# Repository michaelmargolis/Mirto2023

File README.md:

# Mirto2023
This repository contains software and CAD files for the 2023 version of
the Middlesex University robot platform used for CS and outreach.

This version supports the following variants:
* CS Mirto using Teensy 3.2 board and Raspberry Pi 
  * Teensy drives robot hardware
  * Pi supports robot logic in high level language (python, racket etc)
  * Communication between teensy and Pi using ASIP protocol (see ASIP 1.2 repo)
  * two legacy PCBs are supported:
    * Mirto2016 board that uses Toshiba TB6612FNG H-Bridge
    * Mirto2018 board using TI DRV8833 H-Bridge
  
* CS Mirto using Pico 2040 and Raspbery Pi
  * similar to above but using Pico instead of Teensy
  
* Outreach Mirto using Pico WiFI
  * Uses same Pico PCB as CS pico but without Raspberry pi
  * ASIP protocol over WiFI connects to Scratch or similar
  
* Outreach Mirto using Arduino Wifi R2
  * Uses custom shield for H-Bridge and other robot hardware support
  * ASIP protocol over WiFI connects to Scratch or similar
  
* Standalone Mirto
  * This comprises any of the above without the Raspberry PI
  * Robot logic onboard in C++ or micropython depending on microcontroller

See the ASIP 1.2 repository for code needed for the CS version 

A research paper providing context for use of this robot at Middlesex University can be found here https://eprints.mdx.ac.uk/24368/

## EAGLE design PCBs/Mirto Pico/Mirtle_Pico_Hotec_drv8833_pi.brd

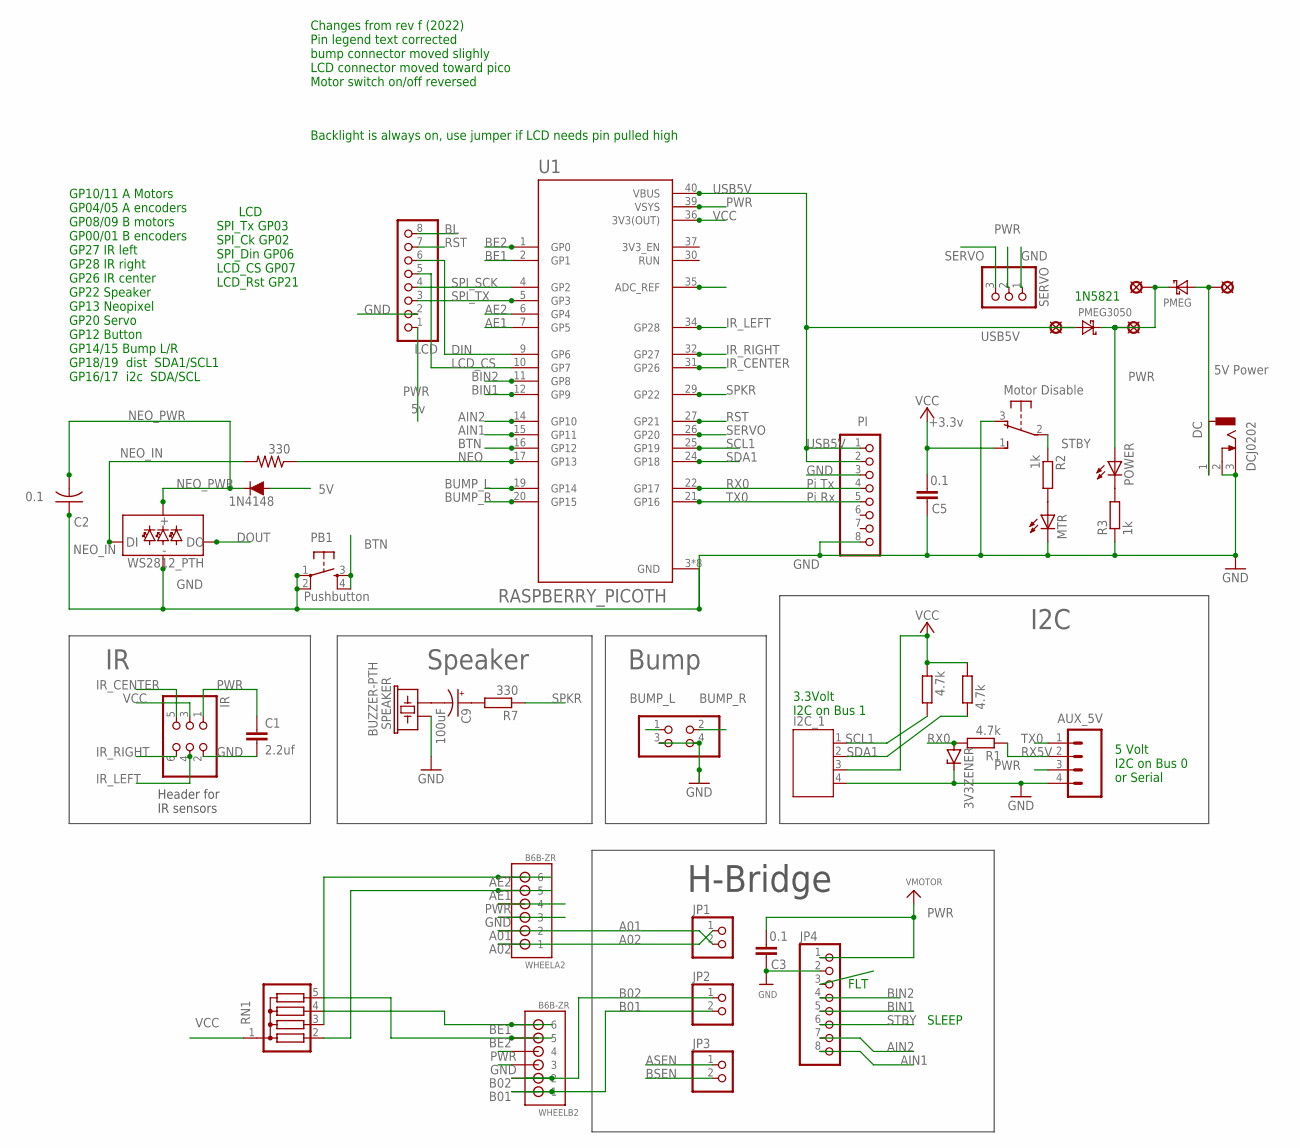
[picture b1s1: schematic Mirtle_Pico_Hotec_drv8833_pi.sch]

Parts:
3V3ZENER: ZENER-DIODEZD-5; ZDIO-5
AUX_5V: CONN_04; 1X04
BUMP: PINHD-2X2; 2X02
C1: 2.2uf; C5B2.5
C2: 0.1; C025-024X044
C3, C5: 0.1; CAP-PTH-SMALLEZ
C9: 100uF; E2,5-5
D1: WS2812_PTH; WS2812B-PTH-KIT
DC: DCJ0202
I2C_1: JST-PH4
IN4148: 200mA/100V/1V; DIODE-1N4148
IR: PINHD-2X3; 2X03
JP1, JP2, JP3: HEADER-1X2ROUND; 1X02_ROUND
JP4: HEADER-1X870MIL; 1X08_ROUND_70
LCD: PINHD-1X8BIG; 1X08-BIG
LSP1, LSP2, LSP3, LSP4: SE14
MTR: LED3MM
PB1: TAC_SWITCHPTH; TACTILE-PTH
PI: PINHD-1X8BIG; 1X08-BIG
PMEG, PMEG3050: DIODE-SCHOTTKY-SMA; SMA
POWER: LED3MM
R1, R4, R5: 4.7k; 0204/5
R2, R3: 1k; 0204/5
R7, R12: 330; 0204/5
RN1: G04R; SIL5
SERVO: PINHD-1X3; 1X03
SPEAKER: BUZZER-PTH; BUZZER-12MM
SW1: OS102011MA1Q
U1: RASPBERRY_PICOTH; PICO-PKG-TH_MM
WHEELA2: B6B-ZR
WHEELB2: B6B-ZR

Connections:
5VIN: DC.1, LSP3.MP, PMEG.A
A01: JP1.2, WHEELA2.2
A02: JP1.1, WHEELA2.1
AE1: RN1.2, U1.7 (GP5), WHEELA2.5
AE2: RN1.3, U1.6 (GP4), WHEELA2.6
AIN1: JP4.8, U1.15 (GP11)
AIN2: JP4.7, U1.14 (GP10)
ASEN: JP3.1
B01: JP2.2, WHEELB2.1
B02: JP2.1, WHEELB2.2
BE1: RN1.4, U1.2 (GP1), WHEELB2.6
BE2: RN1.5, U1.1 (GP0), WHEELB2.5
BIN1: JP4.5, U1.12 (GP9)
BIN2: JP4.4, U1.11 (GP8)
BL: LCD.8
BSEN: JP3.2
BTN: PB1.3, PB1.4, U1.16 (GP12)
BUMP_L: BUMP.1, U1.19 (GP14)
BUMP_R: BUMP.2, U1.20 (GP15)
DIN: LCD.6, U1.9 (GP6)
DOUT: D1.DO
GND: 3V3ZENER.C, AUX_5V.4, BUMP.3, BUMP.4, C1.2, C2.1, C3.1, C5.1, D1.GND, DC.2, DC.3, I2C_1.4, IR.2, JP4.2, LCD.2, MTR.K (C), PB1.1, PB1.2, PI.3, PI.8, R3.1, SERVO.1, SPEAKER.+ (1), SW1.3 (O), U1.3 (GND), U1.8 (GND), U1.13 (GND), U1.18 (GND), U1.23 (GND), U1.28 (GND), U1.33 (GND), U1.38 (GND), WHEELA2.3, WHEELB2.3
IR_CENTER: IR.5, U1.31 (GP26)
IR_LEFT: IR.4, U1.34 (GP28)
IR_RIGHT: IR.6, U1.32 (GP27)
LCD_CS: LCD.5, U1.10 (GP7)
unnamed: POWER.K (C), R3.2
unnamed: MTR.A, R2.2
unnamed: C9.-, SPEAKER.- (2)
unnamed: C9.+, R7.2
NEO: R12.1, U1.17 (GP13)
NEO_IN: D1.DI, R12.2
NEO_PWR: C2.2, D1.VCC, IN4148.C
PWR: AUX_5V.3, C1.1, C3.2, IN4148.A, IR.1, JP4.1, LCD.1, LSP2.MP, LSP4.MP, PMEG.C, PMEG3050.C, POWER.A, SERVO.2, U1.39 (VSYS), WHEELA2.4, WHEELB2.4
RST: LCD.7, U1.27 (GP21)
RX0: 3V3ZENER.A, PI.4, R1.2, U1.22 (GP17)
RX5V: AUX_5V.2, R1.1
SCL1: I2C_1.1, R5.1, U1.25 (GP19)
SDA1: I2C_1.2, R4.1, U1.24 (GP18)
SERVO: SERVO.3, U1.26 (GP20)
SPI_SCK: LCD.4, U1.4 (GP2)
SPI_TX: LCD.3, U1.5 (GP3)
SPKR: R7.1, U1.29 (GP22)
STBY: JP4.6, R2.1, SW1.2
TX0: AUX_5V.1, PI.5, U1.21 (GP16)
USB5V: LSP1.MP, PI.1, PI.2, PMEG3050.A, U1.40 (VBUS)
VCC: C5.2, I2C_1.3, IR.3, R4.2, R5.2, RN1.1, SW1.1 (S), U1.36 (3V3(OUT))

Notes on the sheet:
Motor Disable
5V Power
+3.3v
Header for IR sensors
Pushbutton
I2C
1N4148
Speaker
H-Bridge
FLT
SLEEP
GP10/11 A Motors GP04/05 A encoders GP08/09 B motors GP00/01 B encoders GP27 IR left GP28 IR right GP26 IR center GP22 Speaker GP13 Neopixel GP20 Servo GP12 Button GP14/15 Bump L/R GP18/19 dist SDA1/SCL1 GP16/17 i2c SDA/SCL
1N5821
Backlight is always on, use jumper if LCD needs pin pulled high
Changes from rev f (2022) Pin legend text corrected bump connector moved slighly LCD connector moved toward pico Motor switch on/off reversed
Bump
LCD SPI_Tx GP03 SPI_Ck GP02 SPI_Din GP06 LCD_CS GP07 LCD_Rst GP21
Pi Tx
Pi Rx
5 Volt I2C on Bus 0 or Serial
3.3Volt I2C on Bus 1

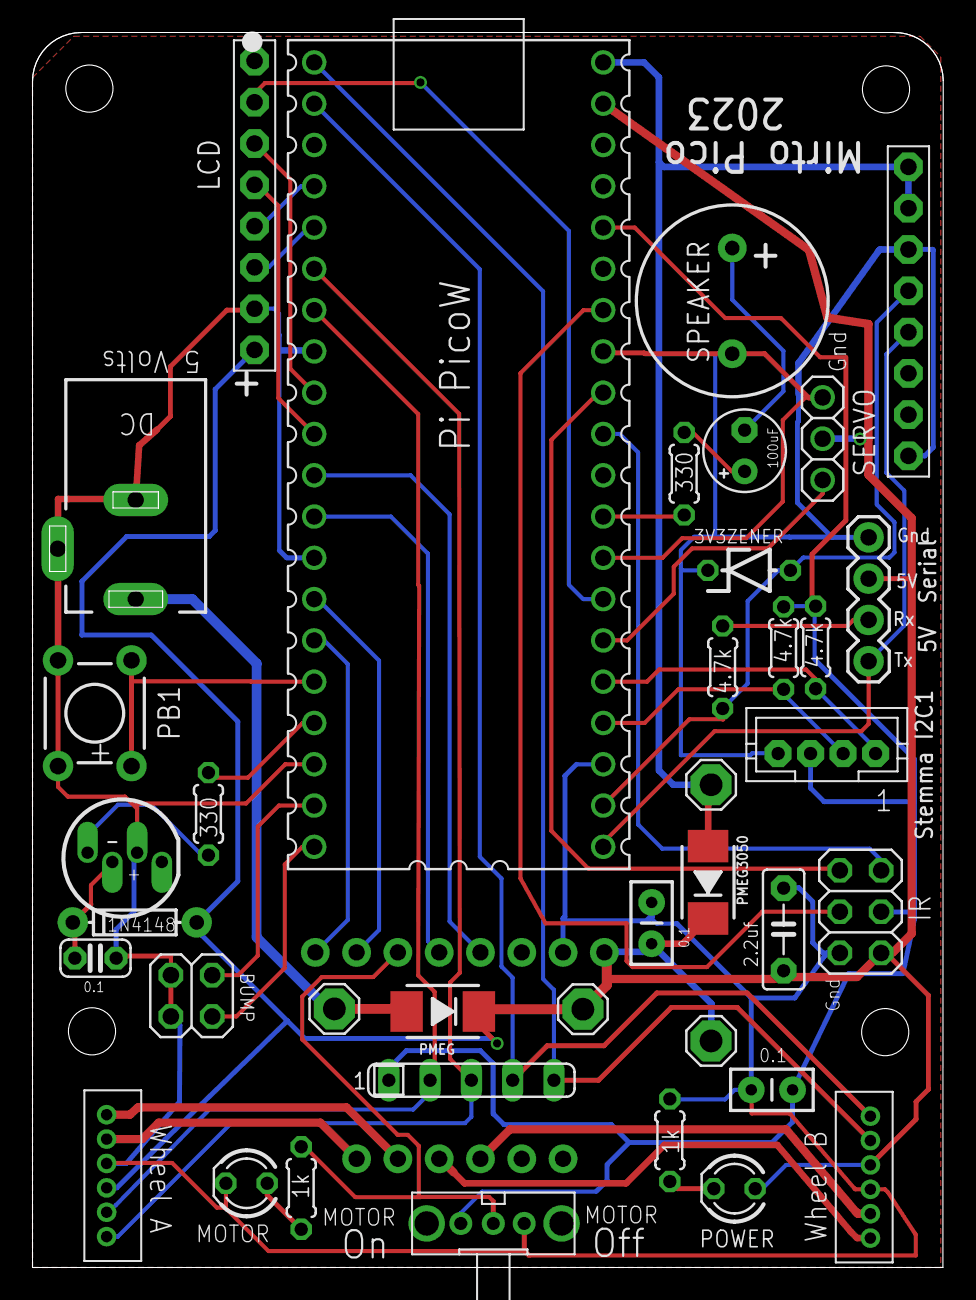
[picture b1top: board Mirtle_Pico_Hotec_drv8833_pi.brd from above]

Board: 2 copper layers, 56.0 x 76.0 mm, 42 parts (0 on the bottom side), 43 nets.

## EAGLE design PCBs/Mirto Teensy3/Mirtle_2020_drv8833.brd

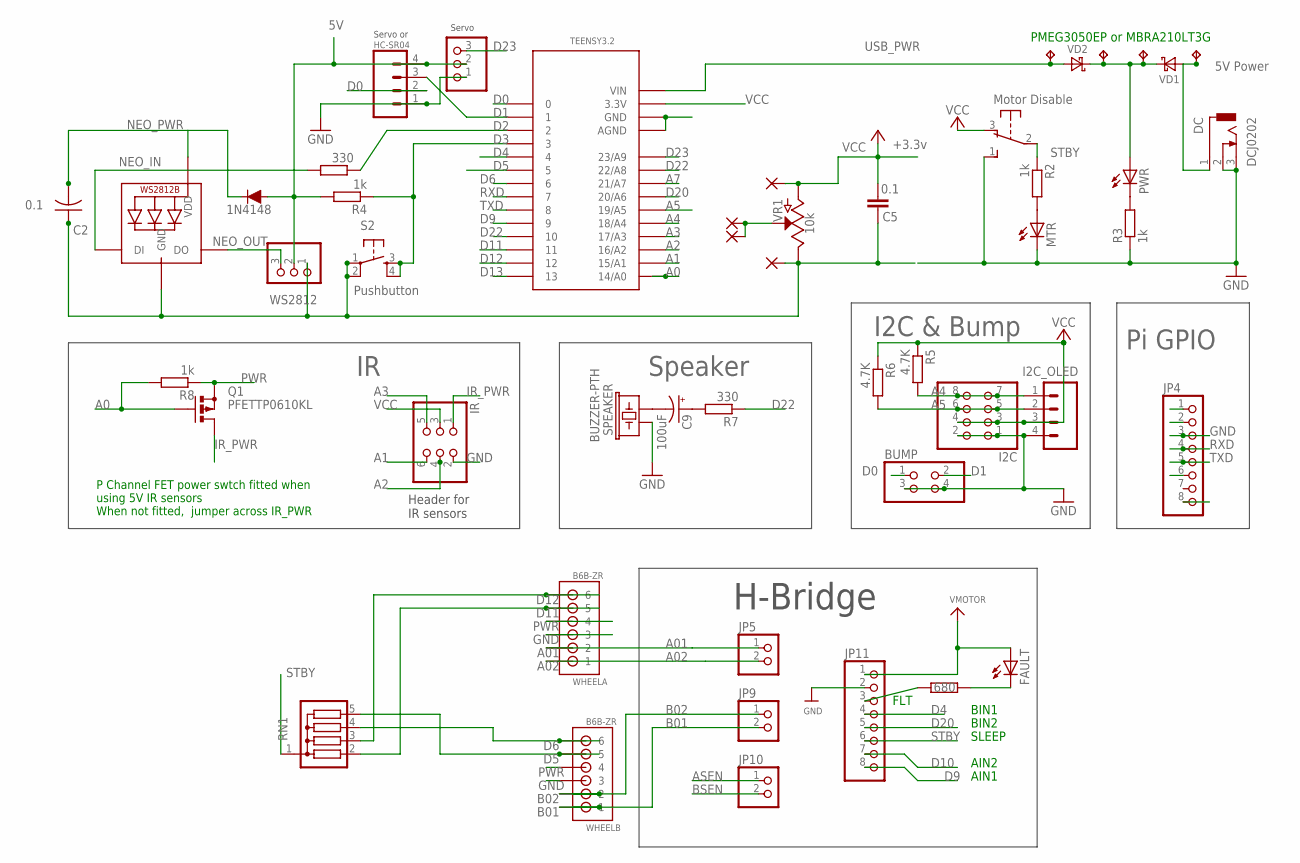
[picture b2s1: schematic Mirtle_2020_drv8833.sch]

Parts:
BUMP: PINHD-2X2; 2X02
C2: 0.1; C025-024X044
C5: 0.1; CAP-PTH-SMALLEZ
C9: 100uF; E2,5-5
DC: DCJ0202
EXT: PINHD-1X3; 1X03
FAULT: LED3MM
HC-SR04: CONN_04; 1X04
I2C: PINHD-2X4; 2X04
I2C_OLED: CONN_04; 1X04
IN4148: 200mA/100V/1V; DIODE-1N4148
IR: PINHD-2X3; 2X03
JP4: PINHD-1X8BIG; 1X08-BIG
JP5, JP9, JP10: HEADER-1X2ROUND; 1X02_ROUND
JP11: HEADER-1X870MIL; 1X08_ROUND_70
LED1: WS2812B5050; WS2812B
MTR: LED3MM
PAD6, PAD7, PAD8, PAD9: 1,6/0,8
PWR: LED3MM
Q1: PFETTP0610KL; TO92-OVAL
R1: 680; 0204/7
R2, R3, R4, R8: 1k; 0204/5
R5, R6: 4.7K; 0204/7
R7, R12: 330; 0204/7
RN1: G04R; SIL5
S2: TAC_SWITCHPTH; TACTILE-PTH
SPEAKER: BUZZER-PTH; BUZZER-12MM
SW1: OS102011MA1Q
TEENSY3.2: TEENSY_3.0_BASIC
TP1, TP2, TP3, TP4: TPPAD1-13; P1-13
VD1, VD2: DIODE-SCHOTTKY-SMA; SMA
VR1: 10k; POT-PTH-ALPS-KIT
WHEELA: B6B-ZR
WHEELB: B6B-ZR
WS2812: PINHD-1X3; 1X03

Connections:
5VIN: DC.1, TP1.TP, VD1.A
A0: Q1.2 (G), R8.2, TEENSY3.2.14/A0
A1: IR.6, TEENSY3.2.15/A1
A01: JP5.1, WHEELA.2
A2: IR.4, TEENSY3.2.16/A2
A02: JP5.2, WHEELA.1
A3: IR.5, TEENSY3.2.17/A3
A4: I2C.7, I2C.8, I2C_OLED.1, R5.2, TEENSY3.2.18/A4
A5: I2C.5, I2C.6, I2C_OLED.2, R6.2, TEENSY3.2.19/A5
A7: PAD6.1, PAD9.1, TEENSY3.2.21/A7, VR1.P$2 (S)
ASEN: JP10.1
B01: JP9.2, WHEELB.1
B02: JP9.1, WHEELB.2
BSEN: JP10.2
D0: BUMP.1, HC-SR04.2, TEENSY3.2.0
D1: BUMP.2, HC-SR04.3, TEENSY3.2.1
D2: R12.1, TEENSY3.2.2
D3: R4.1, S2.3, S2.4, TEENSY3.2.3
D4: JP11.4, TEENSY3.2.4
D5: RN1.5, TEENSY3.2.5, WHEELB.5
D6: RN1.4, TEENSY3.2.6, WHEELB.6
D9: JP11.8, TEENSY3.2.9
D10: JP11.7, TEENSY3.2.10
D11: RN1.2, TEENSY3.2.11, WHEELA.5
D12: RN1.3, TEENSY3.2.12, WHEELA.6
D13: TEENSY3.2.13
D20: JP11.5, TEENSY3.2.20/A6
D22: R7.1, TEENSY3.2.22/A8
D23: EXT.3, TEENSY3.2.23/A9
GND: BUMP.3, BUMP.4, C2.1, C5.1, DC.2, DC.3, EXT.1, HC-SR04.1, I2C.1, I2C.2, I2C_OLED.4, IR.2, JP4.3, JP4.8, JP11.2, LED1.3-GND (GND), MTR.K (C), PAD8.1, R3.1, S2.1, S2.2, SPEAKER.+ (1), SW1.1 (S), TEENSY3.2.AGND, TEENSY3.2.GND, VR1.P$1 (E), WHEELA.3, WHEELB.3, WS2812.1
IR_PWR: IR.1, Q1.3 (D)
unnamed: JP11.3, R1.1
unnamed: FAULT.K (C), R1.2
unnamed: PWR.K (C), R3.2
unnamed: MTR.A, R2.2
unnamed: C9.-, SPEAKER.- (2)
unnamed: C9.+, R7.2
NEO_IN: LED1.4-DIN (DI), R12.2
NEO_OUT: LED1.2-DOUT (DO), WS2812.3
NEO_PWR: C2.2, IN4148.C, LED1.1-VDD (VDD)
PWR: EXT.2, FAULT.A, HC-SR04.4, IN4148.A, JP4.1, JP4.2, JP11.1, PWR.A, Q1.1 (S), R4.2, R8.1, TP2.TP, TP3.TP, VD1.C, VD2.C, WHEELA.4, WHEELB.4, WS2812.2
RXD: JP4.4, TEENSY3.2.7
STBY: JP11.6, R2.1, RN1.1, SW1.2
TXD: JP4.5, TEENSY3.2.8
USB_PWR: TEENSY3.2.VIN, TP4.TP, VD2.A
VCC: C5.2, I2C.3, I2C.4, I2C_OLED.3, IR.3, PAD7.1, R5.1, R6.1, SW1.3 (O), TEENSY3.2.3.3V, VR1.P$3 (A)

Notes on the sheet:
Motor Disable
5V Power
+3.3v
Servo or
Header for IR sensors
Pushbutton
H-Bridge
Pi GPIO
I2C & Bump
PMEG3050EP or MBRA210LT3G
P Channel FET power swtch fitted when using 5V IR sensors When not fitted, jumper across IR_PWR
1N4148
FLT
BIN1
BIN2
SLEEP
AIN2
AIN1
Servo
Speaker

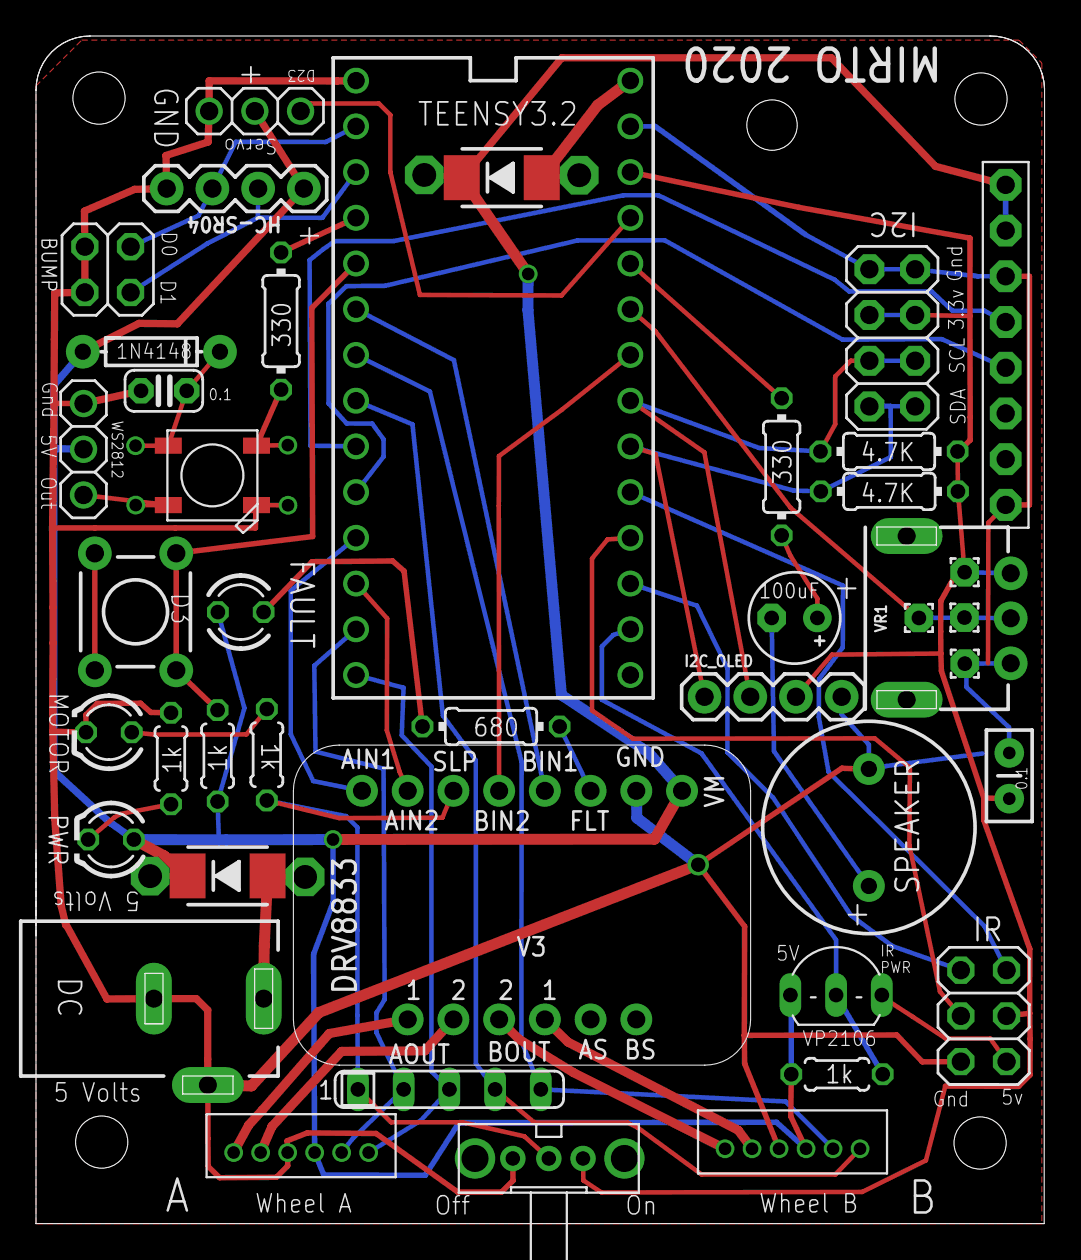
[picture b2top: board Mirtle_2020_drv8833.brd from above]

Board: 4 copper layers, 56.0 x 66.0 mm, 49 parts (0 on the bottom side), 43 nets.

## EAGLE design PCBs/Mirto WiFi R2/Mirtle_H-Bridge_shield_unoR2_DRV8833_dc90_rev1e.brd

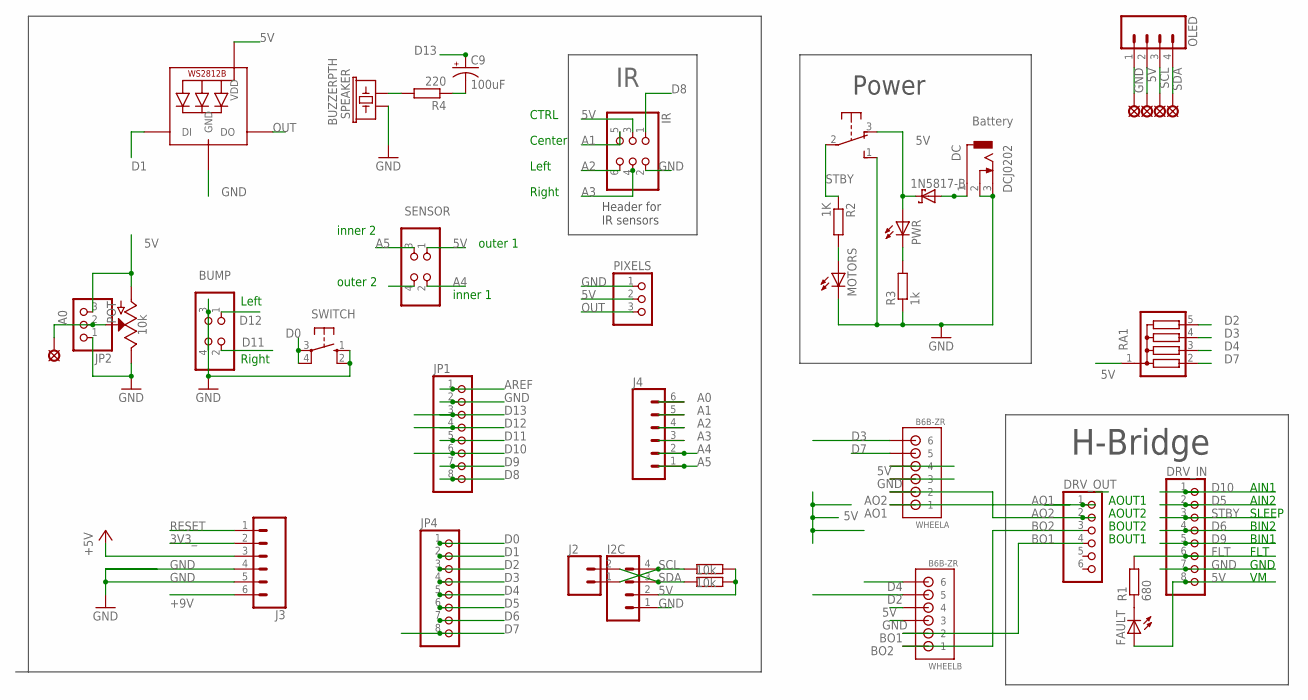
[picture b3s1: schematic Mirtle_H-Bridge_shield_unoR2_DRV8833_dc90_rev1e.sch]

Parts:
BUMP: PINHD-2X2; 2X02
C9: 100uF; E2,5-5
D1: 1N5817-B; DO41-7.6
DC: DCJ0202
DRV_IN: HEADER-1X870MIL; 1X08_ROUND_70
DRV_OUT: PINHD-1X6CLEAN; 1X06-CLEAN
FAULT: LED3MM
I2C: CONN_04; 1X04
IR: PINHD-2X3; 2X03
J2: CONN_02; 1X02
J3, J4: CONN_06NO_SILK_FEMALE_PTH; 1X06_NO_SILK
JP1, JP4: PINHD-1X8CLEANBIG; 1X08-CLEANBIG
JP2: PINHD-1X3CB; 1X03-CLEANBIG
LED1: WS2812B5050; WS2812B
LSP1, LSP13, LSP14, LSP15, LSP16: LSP10
MOTORS: LED3MM
OLED: CONN_04; 1X04
PIXELS: PINHD-1X3; 1X03
POT: 10k; POT-PTH-ALPS
PWR: LED3MM
R1: 680; 0204/5
R2: 1K; 0204/5
R3: 1k; 0204/5
R4: 220; 0204/5
R5, R6: 10k; 0204/5
RA1: G04R; SIL5
SENSOR: PINHD-2X2; 2X02
SPEAKER: BUZZERPTH; BUZZER-12MM
SW1: OS102011MA1Q
SWITCH: 10-XX; B3F-10XX
WHEELA: B6B-ZR
WHEELB: B6B-ZR

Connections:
3V3_: J3.2
5V: D1.C, DRV_IN.8, FAULT.A, I2C.2, IR.3, J3.3, JP2.3, LED1.1-VDD (VDD), LSP14.MP, OLED.2, PIXELS.2, POT.P$3 (A), PWR.A, R5.1, R6.1, RA1.1, SENSOR.1, SW1.3 (O), WHEELA.4, WHEELB.4
5VIN: D1.A, DC.1
+9V: J3.6
A0: J4.6, JP2.2, LSP1.MP, POT.P$2 (S)
A1: IR.5, J4.5
A2: IR.6, J4.4
A3: IR.4, J4.3
A4: J4.2, SENSOR.2
A5: J4.1, SENSOR.3
AO1: DRV_OUT.1, WHEELA.1
AO2: DRV_OUT.2, WHEELA.2
AREF: JP1.1
BO1: DRV_OUT.4, WHEELB.2
BO2: DRV_OUT.3, WHEELB.1
D0: JP4.1, SWITCH.3, SWITCH.4 (P1)
D1: JP4.2, LED1.4-DIN (DI)
D2: JP4.3, RA1.5, WHEELB.5
D3: JP4.4, RA1.4, WHEELA.6
D4: JP4.5, RA1.3, WHEELB.6
D5: DRV_IN.2, JP4.6
D6: DRV_IN.4, JP4.7
D7: JP4.8, RA1.2, WHEELA.5
D8: IR.1, JP1.8
D9: DRV_IN.5, JP1.7
D10: DRV_IN.1, JP1.6
D11: BUMP.2, JP1.5
D12: BUMP.1, JP1.4
D13: C9.+, JP1.3
FLT: DRV_IN.6, R1.2
GND: BUMP.3, BUMP.4, DC.2, DC.3, DRV_IN.7, I2C.1, IR.2, J3.4, J3.5, JP1.2, JP2.1, LED1.3-GND (GND), LSP13.MP, MOTORS.K (C), OLED.1, PIXELS.1, POT.P$1 (E), R3.1, SENSOR.4, SPEAKER.+ (1), SW1.1 (S), SWITCH.1 (S), SWITCH.2 (S1), WHEELA.3, WHEELB.3
unnamed: PWR.K (C), R3.2
unnamed: R4.2, SPEAKER.- (2)
unnamed: C9.-, R4.1
unnamed: FAULT.K (C), R1.1
unnamed: MOTORS.A, R2.2
OUT: LED1.2-DOUT (DO), PIXELS.3
RESET: J3.1
SCL: I2C.4, J2.1, LSP15.MP, OLED.3, R5.2
SDA: I2C.3, J2.2, LSP16.MP, OLED.4, R6.2
STBY: DRV_IN.3, R2.1, SW1.2

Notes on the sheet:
Battery
Header for IR sensors
H-Bridge
GND
AIN1
AIN2
SLEEP
BIN1
BIN2
FLT
Center
CTRL
Left
Right
AOUT1
AOUT2
BOUT2
BOUT1
Power
outer 1
outer 2
inner 1
inner 2

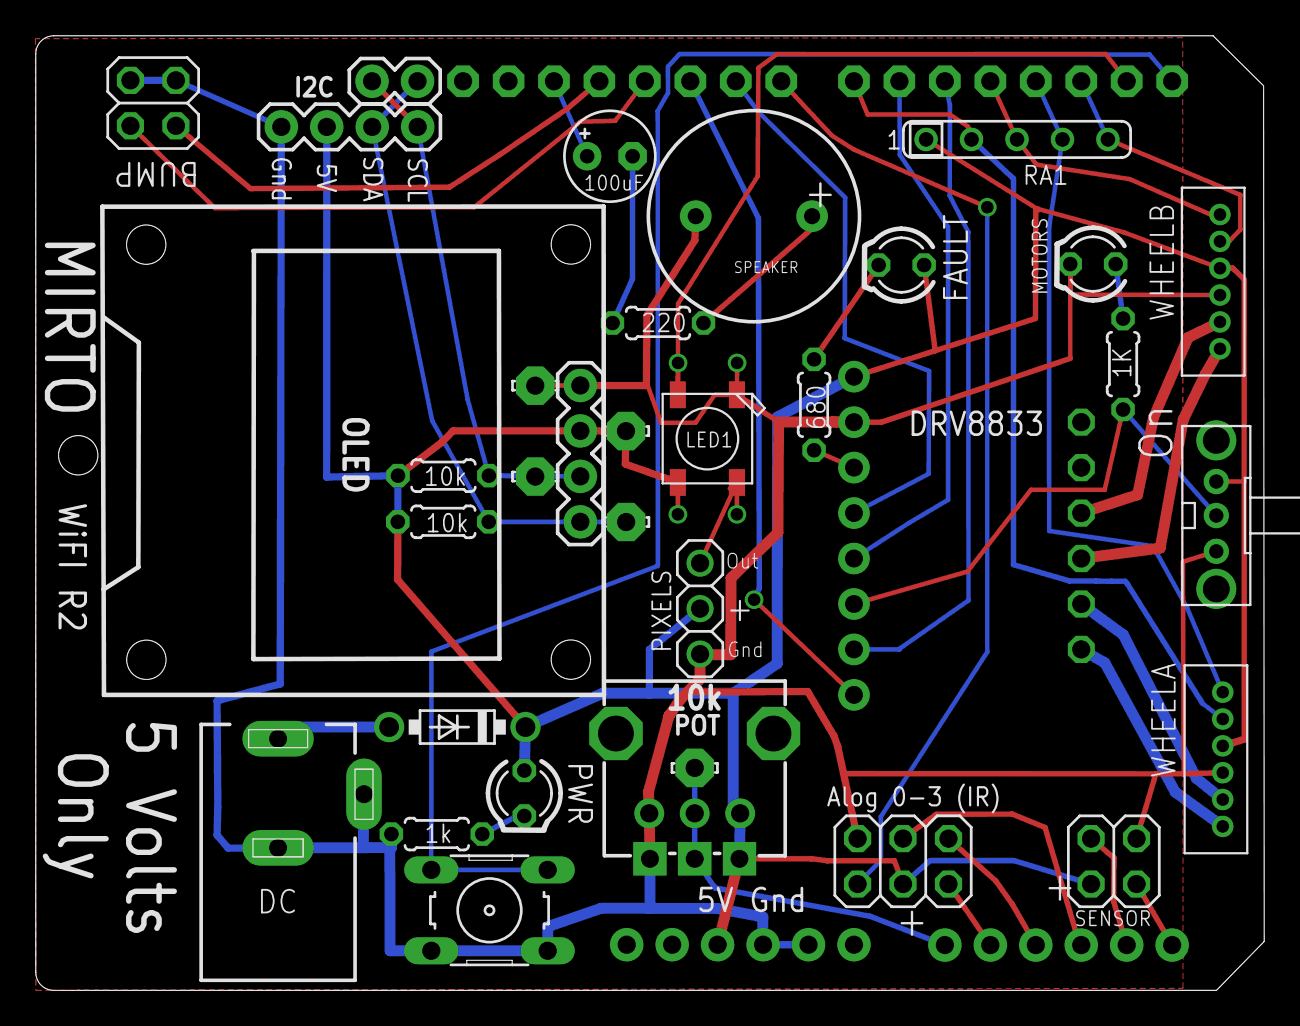
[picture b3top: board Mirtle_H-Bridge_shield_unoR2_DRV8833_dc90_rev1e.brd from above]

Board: 2 copper layers, 68.6 x 53.3 mm, 39 parts (0 on the bottom side), 37 nets.

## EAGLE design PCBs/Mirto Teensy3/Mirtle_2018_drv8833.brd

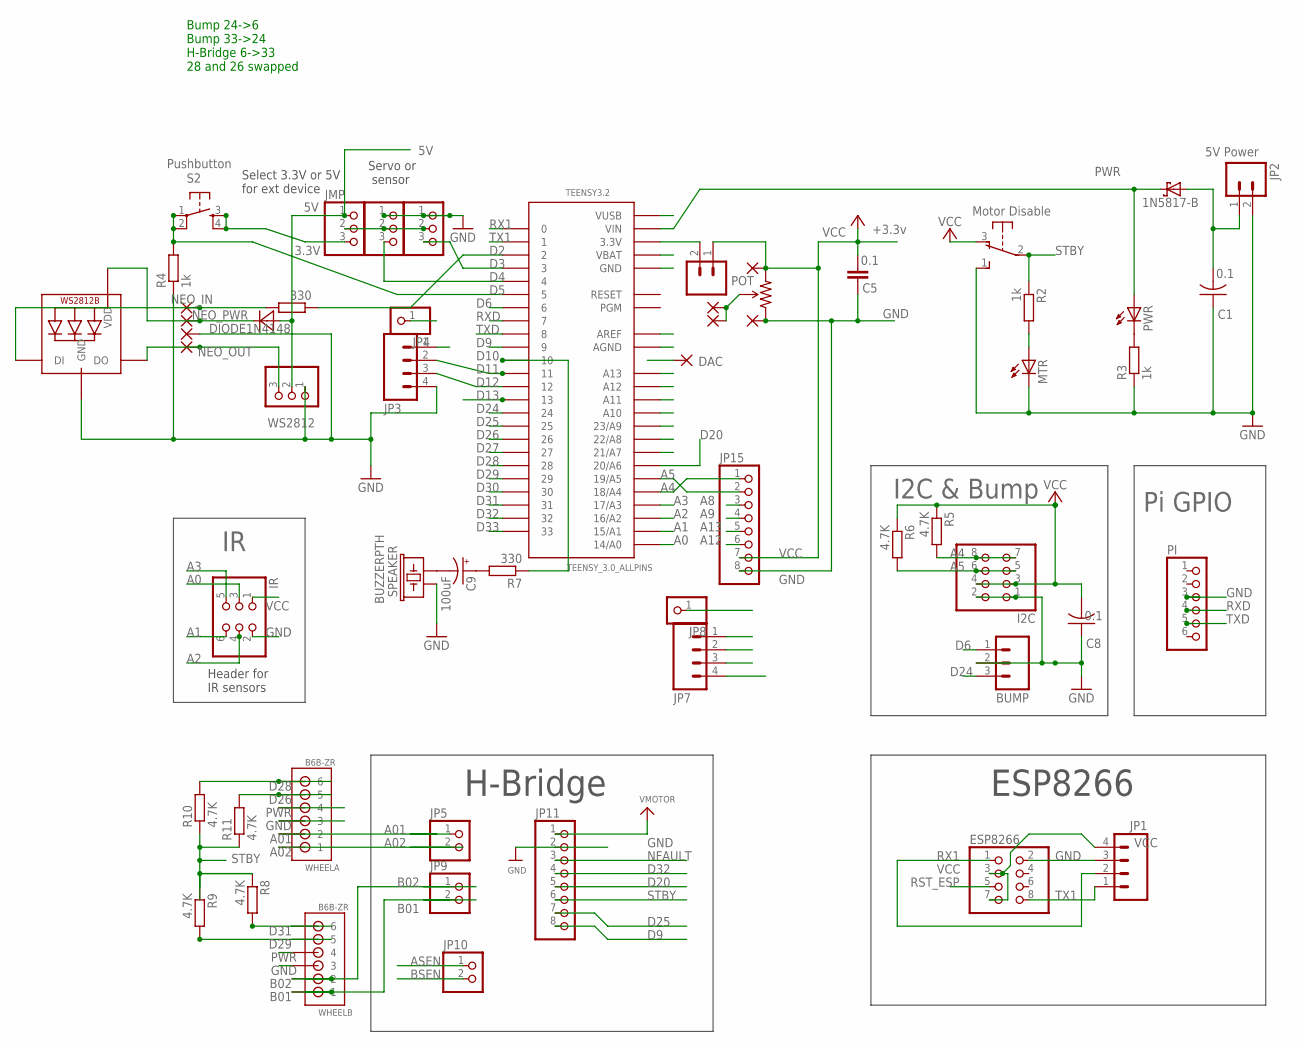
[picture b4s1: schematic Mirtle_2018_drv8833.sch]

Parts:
3V3: M02PTH; 1X02
BUMP: M03SCREW; SCREWTERMINAL-3.5MM-3
C1, C8: 0.1; C025-024X044
C5: 0.1; CAP-PTH-SMALLEZ
C9: 100uF; E2,5-5
D1: 1N5817-B; DO41-7.6
D3: DIODE1N4148; DO-35
DAC: 1,6/0,8
ESP8266: PINHD-2X4; 2X04
EXT, EXT1: PINHD-1X3; 1X03
I2C: PINHD-2X4; 2X04
IR: PINHD-2X3; 2X03
JMP: PINHD-1X3; 1X03
JP1, JP3, JP7: M04PTH; 1X04
JP2: M023.5MM; SCREWTERMINAL-3.5MM-2
JP4, JP8: PINHD-1X1; 1X01
JP5, JP9, JP10: HEADER-1X2ROUND; 1X02_ROUND
JP11: HEADER-1X870MIL; 1X08_ROUND_70
JP15: PINHD-1X8BIG; 1X08-BIG
LED1: WS2812B5050; WS2812B
MTR: LED3MM
PAD2, PAD3, PAD4, PAD5, PAD6, PAD7, PAD8, PAD9: 1,6/0,8
PI: PINHD-1X6; 1X06
POT: TSR-3386; 3386U
PWR: LED3MM
R2, R3, R4: 1k; 0204/7
R5, R6: 4.7K; 0204/7
R7: 330; 0204/7
R8, R9, R10, R11: 4.7K; 0204/5
R12: 330; 0204/5
S2: TAC_SWITCHPTH; TACTILE-PTH
SPEAKER: BUZZERPTH; BUZZER-12MM
SW1: OS102011MA1Q
TEENSY3.2: TEENSY_3.0_ALLPINS
WHEELA: B6B-ZR
WHEELB: B6B-ZR
WS2812: PINHD-1X3; 1X03

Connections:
5VIN: C1.2, D1.A, JP2.1
A0: IR.3, TEENSY3.2.14/A0
A1: IR.6, TEENSY3.2.15/A1
A01: JP5.1, WHEELA.2
A2: IR.4, TEENSY3.2.16/A2
A02: JP5.2, WHEELA.1
A3: IR.5, TEENSY3.2.17/A3
A4: I2C.7, I2C.8, JP7.1, JP15.1, R5.2, TEENSY3.2.18/A4
A5: I2C.5, I2C.6, JP8.1, JP15.2, R6.2, TEENSY3.2.19/A5
A7: PAD6.1, PAD9.1, POT.2 (WIPER), TEENSY3.2.21/A7
A8: JP15.3, TEENSY3.2.22/A8
A9: JP15.4, TEENSY3.2.23/A9
A10: TEENSY3.2.A10
A11: TEENSY3.2.A11
A12: JP15.6, TEENSY3.2.A12
A13: JP15.5, TEENSY3.2.A13
ASEN: JP10.1
B01: JP9.2, WHEELB.1
B02: JP9.1, WHEELB.2
BSEN: JP10.2
D2: R12.1, TEENSY3.2.2
D3: EXT.3, TEENSY3.2.3
D4: EXT1.3, TEENSY3.2.4
D5: R4.2, S2.1, S2.2, TEENSY3.2.5
D6: BUMP.1, TEENSY3.2.6
D9: JP11.8, TEENSY3.2.9
D10: R7.1, TEENSY3.2.10
D11: JP3.2, TEENSY3.2.11
D12: JP3.3, TEENSY3.2.12
D13: JP7.4, TEENSY3.2.13
D20: JP11.5, TEENSY3.2.20/A6
D24: BUMP.3, TEENSY3.2.24
D25: JP11.7, TEENSY3.2.25
D26: R11.2, TEENSY3.2.26, WHEELA.5
D27: TEENSY3.2.27
D28: R10.2, TEENSY3.2.28, WHEELA.6
D29: R9.2, TEENSY3.2.29, WHEELB.5
D30: TEENSY3.2.30
D31: R8.2, TEENSY3.2.31, WHEELB.6
D32: JP11.4, TEENSY3.2.32
D33: TEENSY3.2.33
GND: BUMP.2, C1.1, C5.1, C8.1, ESP8266.2, EXT.1, EXT1.1, I2C.1, I2C.2, IR.2, JP1.3, JP2.2, JP3.4, JP7.3, JP11.2, JP15.8, LED1.3-GND (GND), MTR.K (C), PAD4.1, PAD8.1, PI.3, POT.1 (CCW), R3.1, R4.1, SPEAKER.+ (1), SW1.1 (S), TEENSY3.2.AGND, TEENSY3.2.GND, TEENSY3.2.GND1 (GND), TEENSY3.2.GND2 (GND), WHEELA.3, WHEELB.3, WS2812.1
unnamed: PWR.K (C), R3.2
unnamed: 3V3.2, TEENSY3.2.3.3V, TEENSY3.2.3.3V1 (3.3V), TEENSY3.2.3.3V2 (3.3V)
unnamed: MTR.A, R2.2
unnamed: EXT.2, EXT1.2, JMP.2
unnamed: C9.-, SPEAKER.- (2)
unnamed: C9.+, R7.2
NEO_IN: LED1.4-DIN (DI), PAD2.1, R12.2
NEO_OUT: LED1.2-DOUT (DO), PAD5.1, WS2812.3
NEO_PWR: D3.-, LED1.1-VDD (VDD), PAD3.1
NFAULT: JP11.3
PWR: D1.C, D3.+, JMP.1, JP11.1, PWR.A, TEENSY3.2.VIN, WHEELA.4, WHEELB.4, WS2812.2
RST_ESP: ESP8266.5
RX1: ESP8266.1, JP1.2, JP3.1, TEENSY3.2.0
RXD: PI.4, TEENSY3.2.7
STBY: JP11.6, R2.1, R8.1, R9.1, R10.1, R11.1, SW1.2
TX1: ESP8266.8, JP1.1, JP4.1, TEENSY3.2.1
TXD: PI.5, TEENSY3.2.8
VCC: 3V3.1, C5.2, C8.2, ESP8266.3, ESP8266.7, I2C.3, I2C.4, IR.1, JMP.3, JP1.4, JP7.2, JP15.7, PAD7.1, POT.3 (CW), R5.1, R6.1, S2.3, S2.4, SW1.3 (O)

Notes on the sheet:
Motor Disable
5V Power
+3.3v
3.3V
Servo or sensor
Select 3.3V or 5V for ext device
Header for IR sensors
Pushbutton
H-Bridge
ESP8266
Pi GPIO
I2C & Bump
Bump 24->6 Bump 33->24 H-Bridge 6->33 28 and 26 swapped

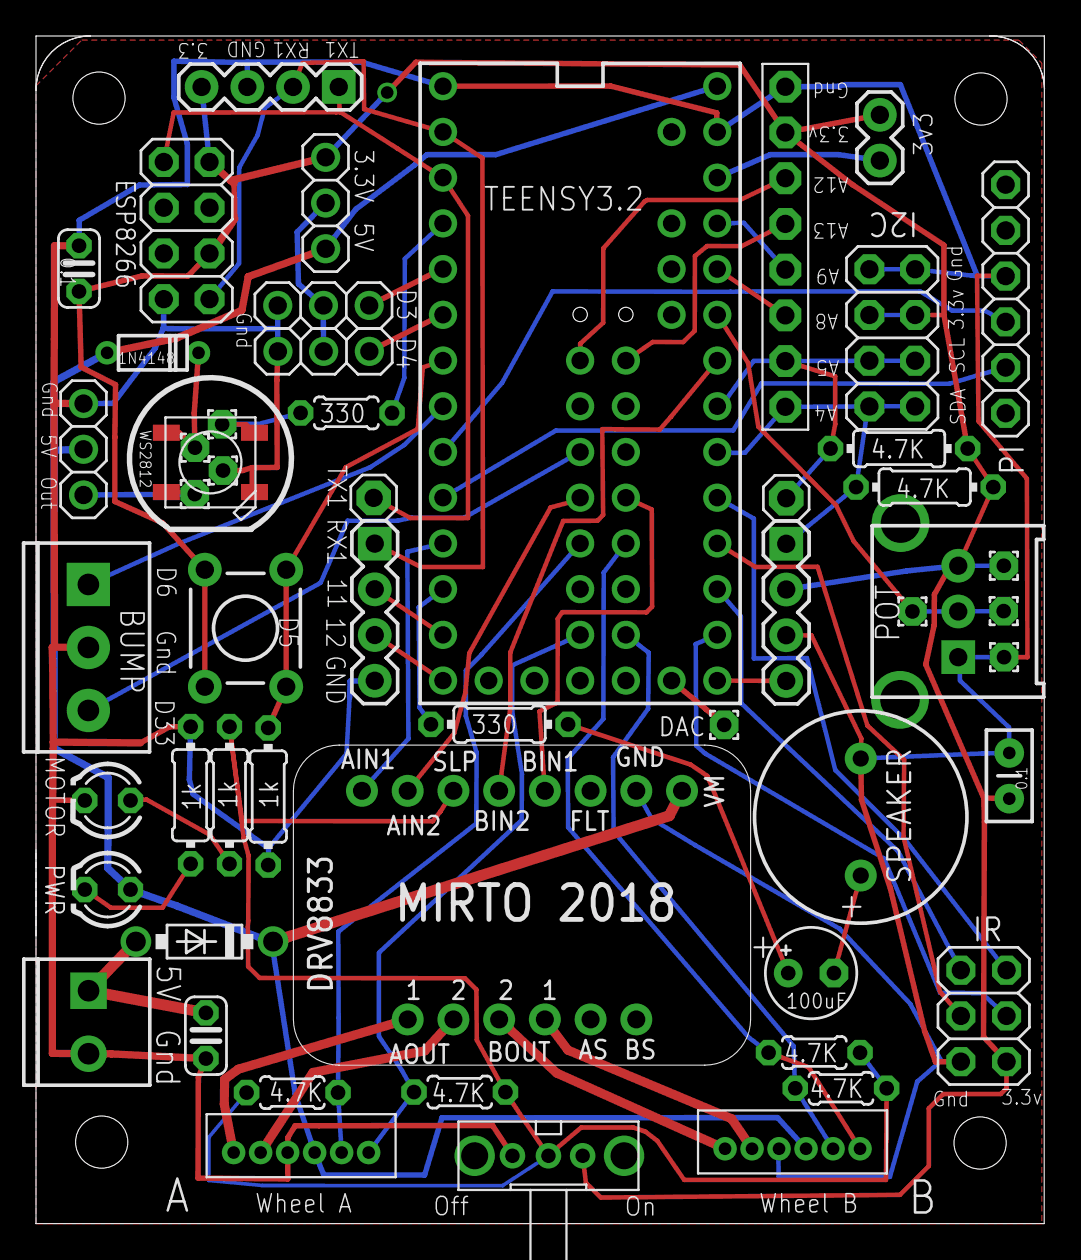
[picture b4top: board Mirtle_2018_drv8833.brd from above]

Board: 2 copper layers, 56.0 x 66.0 mm, 57 parts (0 on the bottom side), 51 nets.

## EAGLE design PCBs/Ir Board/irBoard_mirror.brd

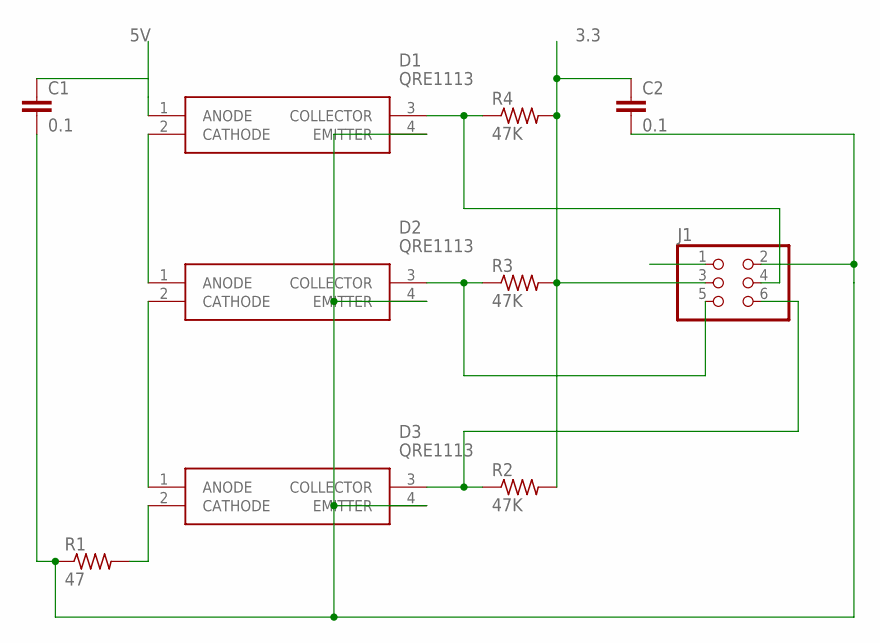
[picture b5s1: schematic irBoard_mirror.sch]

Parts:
C1, C2: 0.1; C025-024X044
D1, D2, D3: QRE1113
J1: PINHD-2X3; 2X03
R1: 47; 0204/5
R2, R3, R4: 47K; 0204/5

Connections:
3.3: C2.1, J1.3, R2.2, R3.2, R4.2
5V: C1.1, D1.1 (ANODE), J1.1
GND: C1.2, C2.2, D1.4 (EMITTER), D2.4 (EMITTER), D3.4 (EMITTER), J1.2, R1.1
unnamed: D2.2 (CATHODE), D3.1 (ANODE)
unnamed: D1.2 (CATHODE), D2.1 (ANODE)
unnamed: D3.2 (CATHODE), R1.2
unnamed: D1.3 (COLLECTOR), J1.4, R4.1
unnamed: D2.3 (COLLECTOR), J1.5, R3.1
unnamed: D3.3 (COLLECTOR), J1.6, R2.1

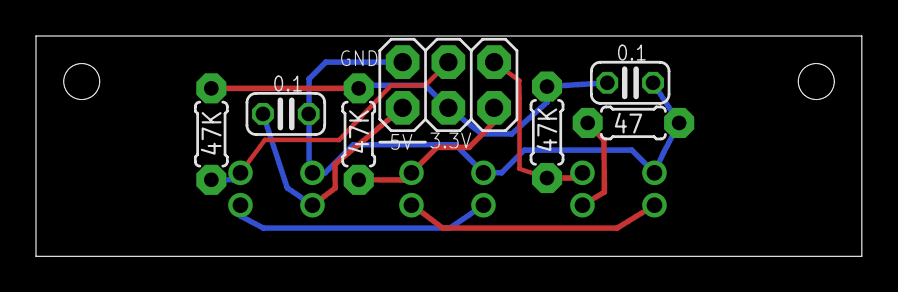
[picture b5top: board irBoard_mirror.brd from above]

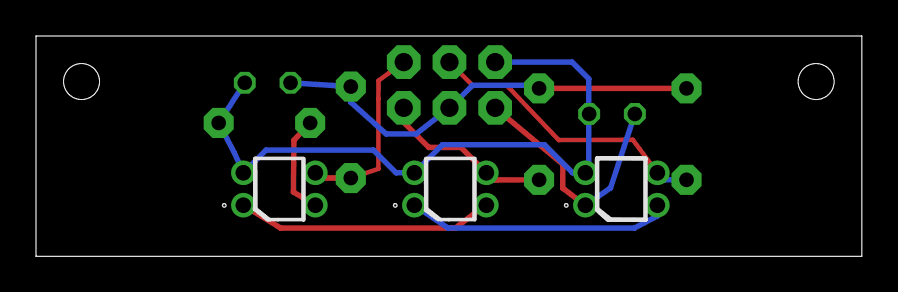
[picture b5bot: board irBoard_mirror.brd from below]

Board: 4 copper layers, 45.9 x 12.2 mm, 10 parts (3 on the bottom side), 9 nets.

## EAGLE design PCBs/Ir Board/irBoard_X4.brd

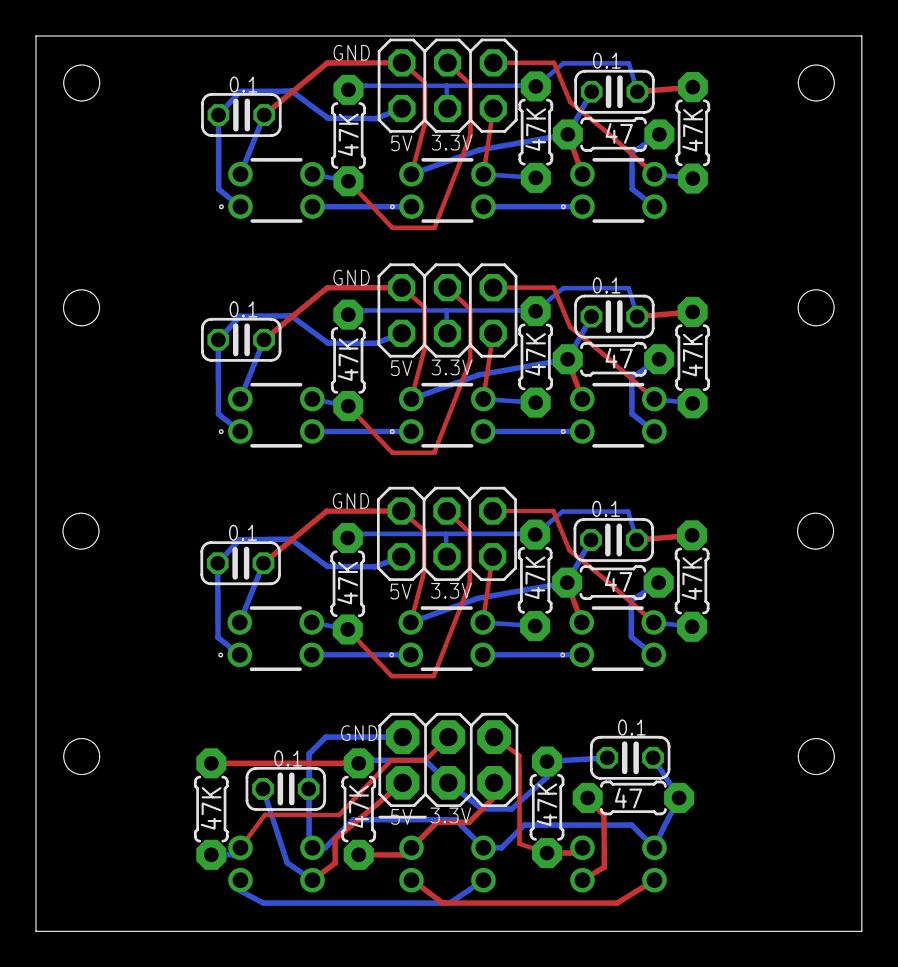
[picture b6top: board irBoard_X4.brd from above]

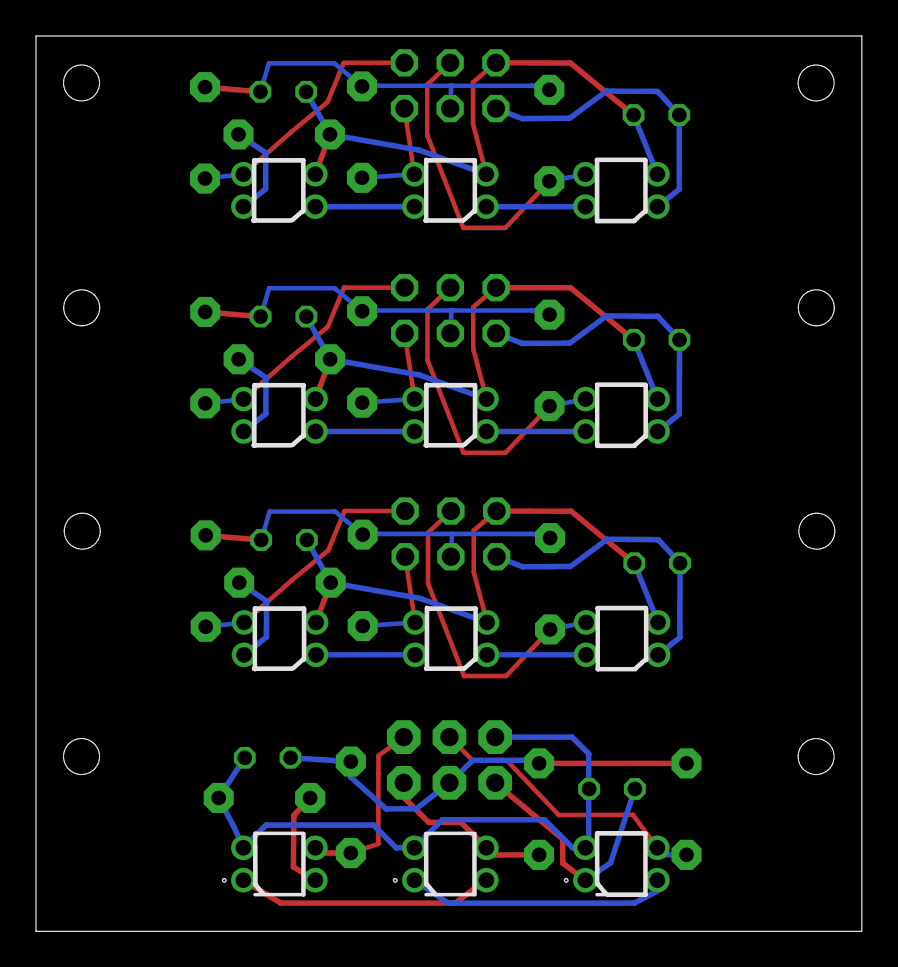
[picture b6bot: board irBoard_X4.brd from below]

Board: 4 copper layers, 45.9 x 49.7 mm, 40 parts (3 on the bottom side), 36 nets.

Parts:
C1, C2, C3, C4, C5, C6, C9, C10: 0.1; C025-024X044
D1, D2, D3, D4, D5, D6, D7, D8, D9, D13, D14, D15: QRE1113
J1: 2X03
JP1, JP2, JP3: 2X03
R1, R5, R9, R17: 47; 0204/5
R2, R3, R4, R6, R7, R8, R10, R11, R12, R18, R19, R20: 47K; 0204/5

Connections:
3.1: C4.1, JP2.3, R6.2, R7.2, R8.2
3.2: C6.1, JP3.3, R10.2, R11.2, R12.2
3.3: C2.1, J1.3, R2.2, R3.2, R4.2
3.5: C10.1, JP1.3, R18.2, R19.2, R20.2
5V: C1.1, D1.1, J1.1
5V1: C3.1, D4.1, JP2.1
5V2: C5.1, D7.1, JP3.1
5V4: C9.1, D13.1, JP1.1
GND: C1.2, C2.2, D1.4, D2.4, D3.4, J1.2, R1.1
GND1: C3.2, C4.2, D4.4, D5.4, D6.4, JP2.2, R5.1
GND2: C5.2, C6.2, D7.4, D8.4, D9.4, JP3.2, R9.1
GND4: C9.2, C10.2, D13.4, D14.4, D15.4, JP1.2, R17.1
unnamed: D2.2, D3.1
unnamed: D1.2, D2.1
unnamed: D5.2, D6.1
unnamed: D3.2, R1.2
unnamed: D4.2, D5.1
unnamed: D6.2, R5.2
unnamed: D1.3, J1.4, R4.1
unnamed: D2.3, J1.5, R3.1
unnamed: D3.3, J1.6, R2.1
unnamed: D4.3, JP2.4, R8.1
unnamed: D5.3, JP2.5, R7.1
unnamed: D6.3, JP2.6, R6.1
unnamed: D8.2, D9.1
unnamed: D7.2, D8.1
unnamed: D9.2, R9.2
unnamed: D7.3, JP3.4, R12.1
unnamed: D8.3, JP3.5, R11.1
unnamed: D9.3, JP3.6, R10.1
unnamed: D14.2, D15.1
unnamed: D13.2, D14.1
unnamed: D15.2, R17.2
unnamed: D13.3, JP1.4, R20.1
unnamed: D14.3, JP1.5, R19.1
unnamed: D15.3, JP1.6, R18.1

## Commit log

2023-05-01 Initial commit of Mirto 2023 files
2023-05-01 Initial commit of readme
2023-05-01 updated link
2023-05-01 added link to build doc
2023-05-01 added mirto 2020 pcb
2023-05-02 added spreadsheet BOM with supplier part numbers
2023-05-02 updated link to BOM
2023-05-02 updated dxf to improve import into lotus cut
2023-05-03 Updated build doc
2023-06-03 updated build doc updated bumper dxf
2023-08-14 updated solidworks parts
2024-08-22 update BOM - added 2.2uf Cap and BAT46 diode

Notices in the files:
parts and their libraries:
SparkFun-Retired: Licensing: Creative Commons ShareAlike 4.0 International - https://creativecommons.org/licenses/by-sa/4.0
SparkFun-Passives: Licensing: CC v3.0 Share-Alike You are welcome to use this library for commercial purposes.
